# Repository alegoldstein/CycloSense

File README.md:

# CycloSense
# EE 327 Spring 2026

This repository contains the files for the firmware, PCB design, and 3D models used to create our bike computer named CycloSense. CycloSense was created to be a bike computer for the everyday bike user, affordable, easy to use, and includes predictive maintenance alerts and offline navigation. 

Objective:
Create a bike computer to provide local navigation, predict maintenence, and display metrics

Steps Taken:
- Load nodes and edges from OpenStreetMap to perform A* algorithm on to find optimal route between two points. 
- Convert node and edge data to a 2D grid based on offset from the map origin to save memory and shorten computing time.
- Process audio from brake and classify as squeaky or normal with a ML model trained on Edge Impulse to alert user of necessary maintenance.
- Display speed, time, brake status, and directions overlayed on a map.
- Mount main system to handlebar and microphone + hall sensor to front fork with custom 3D printed parts.

Outcome:
A bike computer prototype that successfully tracks speed and provides navigation while showcasing predictive maintenance using edge AI.

<p align="center">
  
  <br>
  <em>PCB Schematic</em>
</p>

<p align="center">
  
  <br>
  <em>PCB Rendering</em>
</p>

<table align="center">
  <tr>
    <td align="center">
      <br>
      <em>Full system mounted to handlebar</em>
    </td>
    <td align="center">
      <br>
      <em>Model of 3D printed enclosure</em>
    </td>
  </tr>
</table>

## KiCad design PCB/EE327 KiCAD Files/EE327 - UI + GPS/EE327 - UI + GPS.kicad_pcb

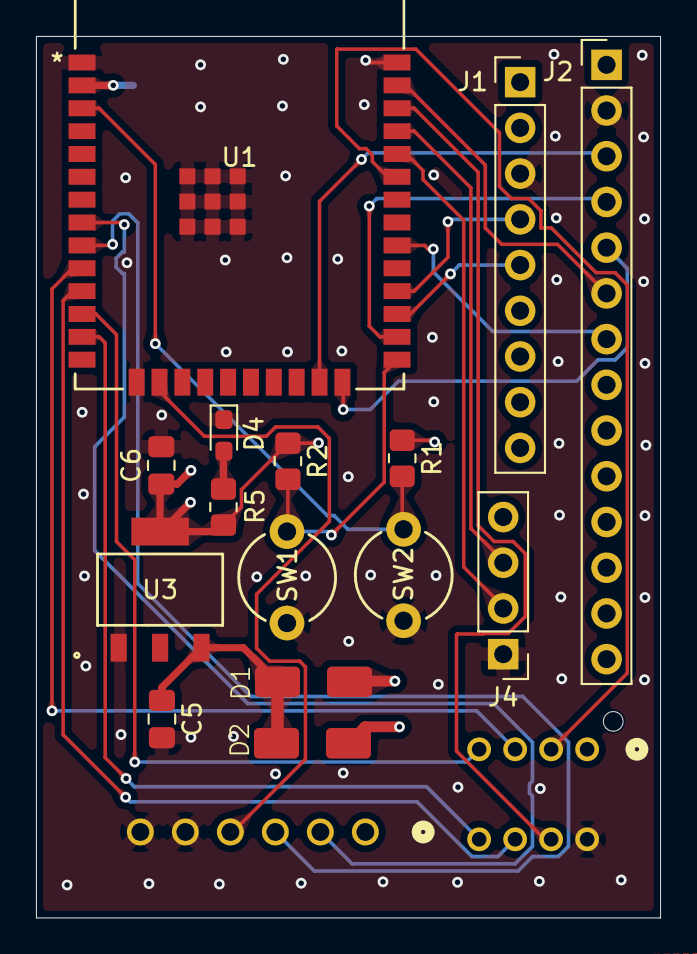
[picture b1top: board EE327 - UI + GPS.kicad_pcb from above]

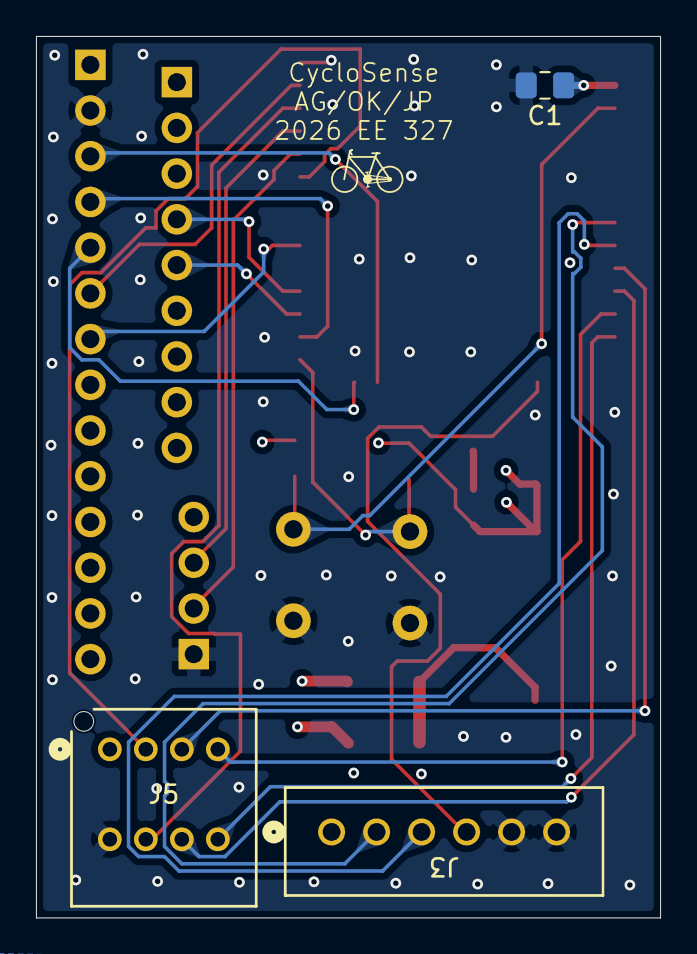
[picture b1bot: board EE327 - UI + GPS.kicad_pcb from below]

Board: 4 copper layers, 34.7 x 49.0 mm, 18 parts (3 on the bottom side), 26 nets.

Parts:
C1: 0.1uF; C_0805_2012Metric_Pad1.18x1.45mm_HandSolder
C5: 1uF; C_0805_2012Metric_Pad1.18x1.45mm_HandSolder
C6: 4.7uF; C_0805_2012Metric_Pad1.18x1.45mm_HandSolder
D1, D2: D_Schottky; Schottky
D4: LED; LED_0603_1608Metric_Pad1.05x0.95mm_HandSolder
J1: Conn_01x09_Socket; PinHeader_1x09_P2.54mm_Vertical
J2: Conn_01x14_Socket; PinHeader_1x14_P2.54mm_Vertical
J3: Conn_01x06_Pin; 1x6 JST
J4: Conn_01x04_Socket; PinHeader_1x04_P2.54mm_Vertical
J5: Conn_01x08_Socket; CONN_B08B-PNDZS-1_JST
R1, R2: 10k; R_0805_2012Metric_Pad1.20x1.40mm_HandSolder
R5: 330R; R_0805_2012Metric_Pad1.20x1.40mm_HandSolder
SW1, SW2: SW_Push; pushbutton
U1: ESP32-WROOM-32E-N4; ESP32­WROOM­32E_EXP
U3: LDL1117S30R; Voltage Regulator

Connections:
+3.3V: C1.1, C6.1, J1.9, J2.1, J2.8, J3.1, R1.1, R2.1, R5.1, U1.2 (3V3), U3.4 (VOUT__1)
/BOOT: R2.2, SW2.2, U1.25 (IO0)
/ESP_RST: R1.2, SW1.2, U1.3 (EN)
/GPS_RX: J1.4, U1.28 (IO17)
/GPS_TX: J1.5, U1.27 (IO16)
/LDO_IN: C5.1, D1.1 (K), D2.1 (K), U3.3 (VIN)
/MIC_SCK: J3.3, U1.9 (IO33)
/MIC_SD: J3.2, U1.8 (IO32)
/PMIC_STAT1: J5.6, U1.11 (IO26)
/PMIC_STAT2: J5.7, U1.12 (IO27)
/PMIC_~INT: J5.5, U1.10 (IO25)
/PMIC_~PG: J5.8, U1.13 (IO14)
/RX0: J4.2, U1.34 (RXD0)
/SCL: J5.4, U1.36 (IO22)
/SDA: J5.3, U1.33 (IO21)
/TFT_CS: J2.3, U1.23 (IO15)
/TFT_DC: J2.5, U1.24 (IO2)
/TFT_MOSI: J2.6, U1.37 (IO23)
/TFT_RST: J2.4, U1.26 (IO4)
/TFT_SCK: J2.7, U1.30 (IO18)
/TX0: J4.3, U1.35 (TXD0)
/Terminal_5V: D2.2 (A), J5.1
/USB_5V: D1.2 (A), J4.4
/WS: J3.4, U1.16 (IO13)
GND: C1.2, C5.2, C6.2, D4.1 (K), J1.3, J2.2, J3.5, J3.6, J4.1, J5.2, SW1.1, SW2.1, U1.1 (GND), U1.15 (GND), U1.38 (GND), U1.39 (GND), U1.40 (GND), U1.41 (GND), U1.42 (GND), U1.43 (GND), U1.44 (GND), U1.45 (GND), U1.46 (GND), U1.47 (GND), U3.1 (GND)
unnamed: D4.2 (A), R5.2

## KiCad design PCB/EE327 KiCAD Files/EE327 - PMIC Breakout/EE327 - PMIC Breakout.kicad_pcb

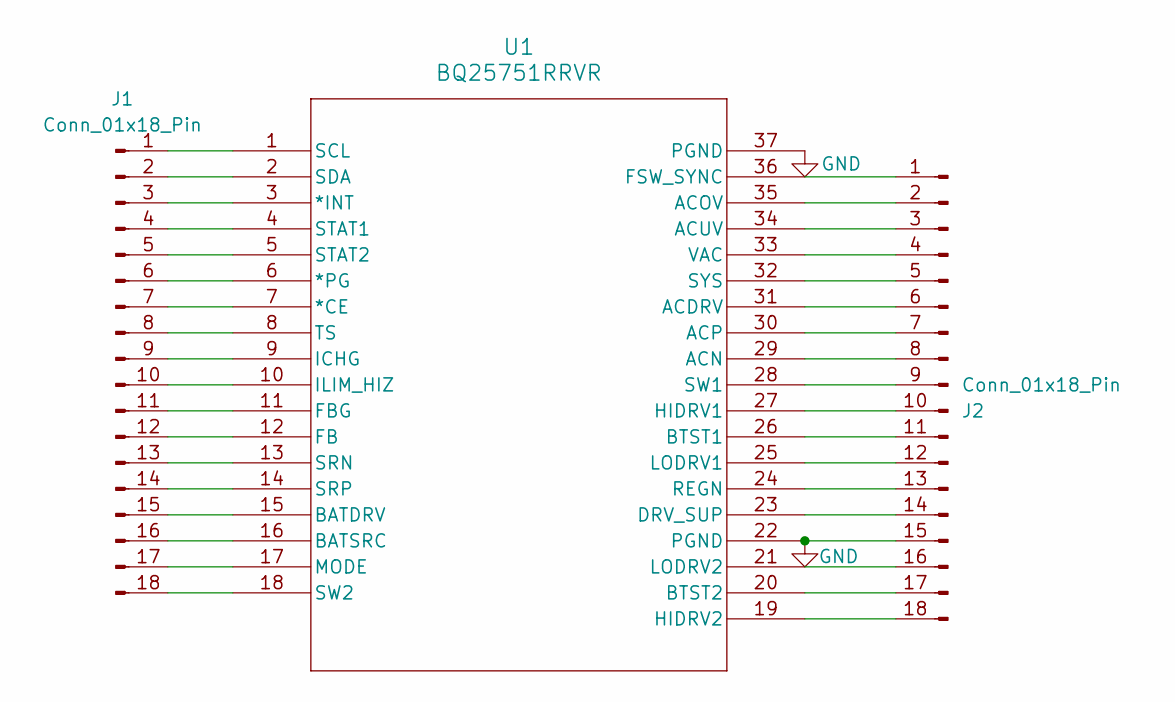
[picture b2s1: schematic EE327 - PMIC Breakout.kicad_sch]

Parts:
J1, J2: Conn_01x18_Pin; PinHeader_1x18_P2.54mm_Vertical
U1: BQ25751RRVR; VQFN36_RRV_TEX

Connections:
GND: J2.15, U1.22 (PGND), U1.37 (PGND)
unnamed: J1.1, U1.1 (SCL)
unnamed: J1.2, U1.2 (SDA)
unnamed: J1.3, U1.3 (*INT)
unnamed: J1.4, U1.4 (STAT1)
unnamed: J1.5, U1.5 (STAT2)
unnamed: J1.6, U1.6 (*PG)
unnamed: J1.7, U1.7 (*CE)
unnamed: J1.8, U1.8 (TS)
unnamed: J1.9, U1.9 (ICHG)
unnamed: J1.10, U1.10 (ILIM_HIZ)
unnamed: J1.11, U1.11 (FBG)
unnamed: J1.12, U1.12 (FB)
unnamed: J1.13, U1.13 (SRN)
unnamed: J1.14, U1.14 (SRP)
unnamed: J1.15, U1.15 (BATDRV)
unnamed: J1.16, U1.16 (BATSRC)
unnamed: J1.17, U1.17 (MODE)
unnamed: J1.18, U1.18 (SW2)
unnamed: J2.1, U1.36 (FSW_SYNC)
unnamed: J2.2, U1.35 (ACOV)
unnamed: J2.3, U1.34 (ACUV)
unnamed: J2.4, U1.33 (VAC)
unnamed: J2.5, U1.32 (SYS)
unnamed: J2.6, U1.31 (ACDRV)
unnamed: J2.7, U1.30 (ACP)
unnamed: J2.8, U1.29 (ACN)
unnamed: J2.9, U1.28 (SW1)
unnamed: J2.10, U1.27 (HIDRV1)
unnamed: J2.11, U1.26 (BTST1)
unnamed: J2.12, U1.25 (LODRV1)
unnamed: J2.13, U1.24 (REGN)
unnamed: J2.14, U1.23 (DRV_SUP)
unnamed: J2.16, U1.21 (LODRV2)
unnamed: J2.17, U1.20 (BTST2)
unnamed: J2.18, U1.19 (HIDRV2)

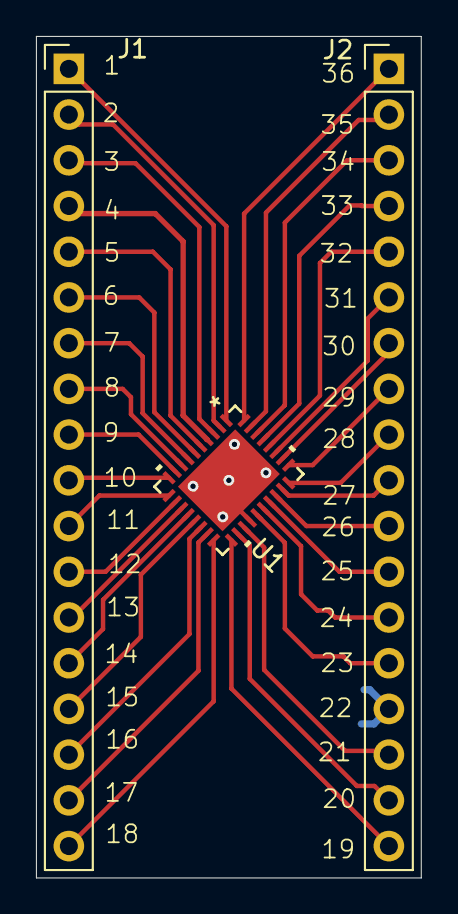
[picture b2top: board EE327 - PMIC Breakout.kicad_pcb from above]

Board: 2 copper layers, 21.4 x 46.8 mm, 3 parts (0 on the bottom side), 36 nets.

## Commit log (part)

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2026-04-15 create gps files and prepare basic functions
2026-04-16 remove uneccesary files
2026-04-21 Update README to include PCB design information
2026-04-21 Add files via upload
    create kicad projects for each subsystem
2026-04-21 Reorganized files
2026-04-21 Reorganized
2026-04-23 create platform.io??
2026-04-23 platform.io
2026-04-24 restructure platform.io project
2026-04-30 gps code
2026-04-30 Added Symbols and Footprints to Battery Management PCB
2026-04-30 Created PMIC PCB Breakout With Manufacturing Files
2026-04-30 navigation start
2026-05-03 Audio classification code
2026-05-05 Revised audio classification firmware
2026-05-05 Fixed library name
2026-05-05 Updated audio classification code
2026-05-12 nav work
2026-05-14 pcb start
2026-05-21 Audio classification and magnetometer code
2026-05-21 Updated user PCB
2026-05-21 Created Power Management Schematic Draft
2026-05-22 Added 2x4 JST footprint
2026-05-22 PCB routing started
2026-05-23 pcb done?
2026-05-23 Updated mic connections
2026-05-24 Resolved lingering DRC errors and generated fabrication files
2026-05-24 Final PCB directory structure
2026-05-24 Updated PCB directory structure
2026-05-24 Deleted predictive maintenance PCB directory (redundant)
2026-05-24 navigationC
2026-05-24 Created final firmware project
2026-05-24 final firmware start
2026-05-31 Changed header file directories and began work on magnetometer driver
2026-05-31 TMAG5273 driver and final data acquisition code
2026-06-02 Magnetometer driver and speed calculation
2026-06-02 arduino
2026-06-03 display speed and map
2026-06-03 working map display and speed calculation in arduino
2026-06-06 this worked on pcb
2026-06-08 not mcuh
2026-06-08 gps features
2026-06-08 Backend software
2026-06-10 Update to PMIC Schematic
2026-06-12 3d models
2026-06-12 stl files
2026-06-12 Final submission
2026-06-12 Final PMIC Schematic
2026-06-12 Final Schematic Version
